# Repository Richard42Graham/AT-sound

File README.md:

# AT-sound 

AKA **ATST**: All terrain sound transport. 

A circuit board controlling a relay when audio cable is active.

## Use

Requires 5V power to operate. Provides 5V and common ground on relay pins when audio is detected.

## Contribution

Please contribute. 

## License

[CERN Open Hardware Licence](https://ohwr.org/cernohl)

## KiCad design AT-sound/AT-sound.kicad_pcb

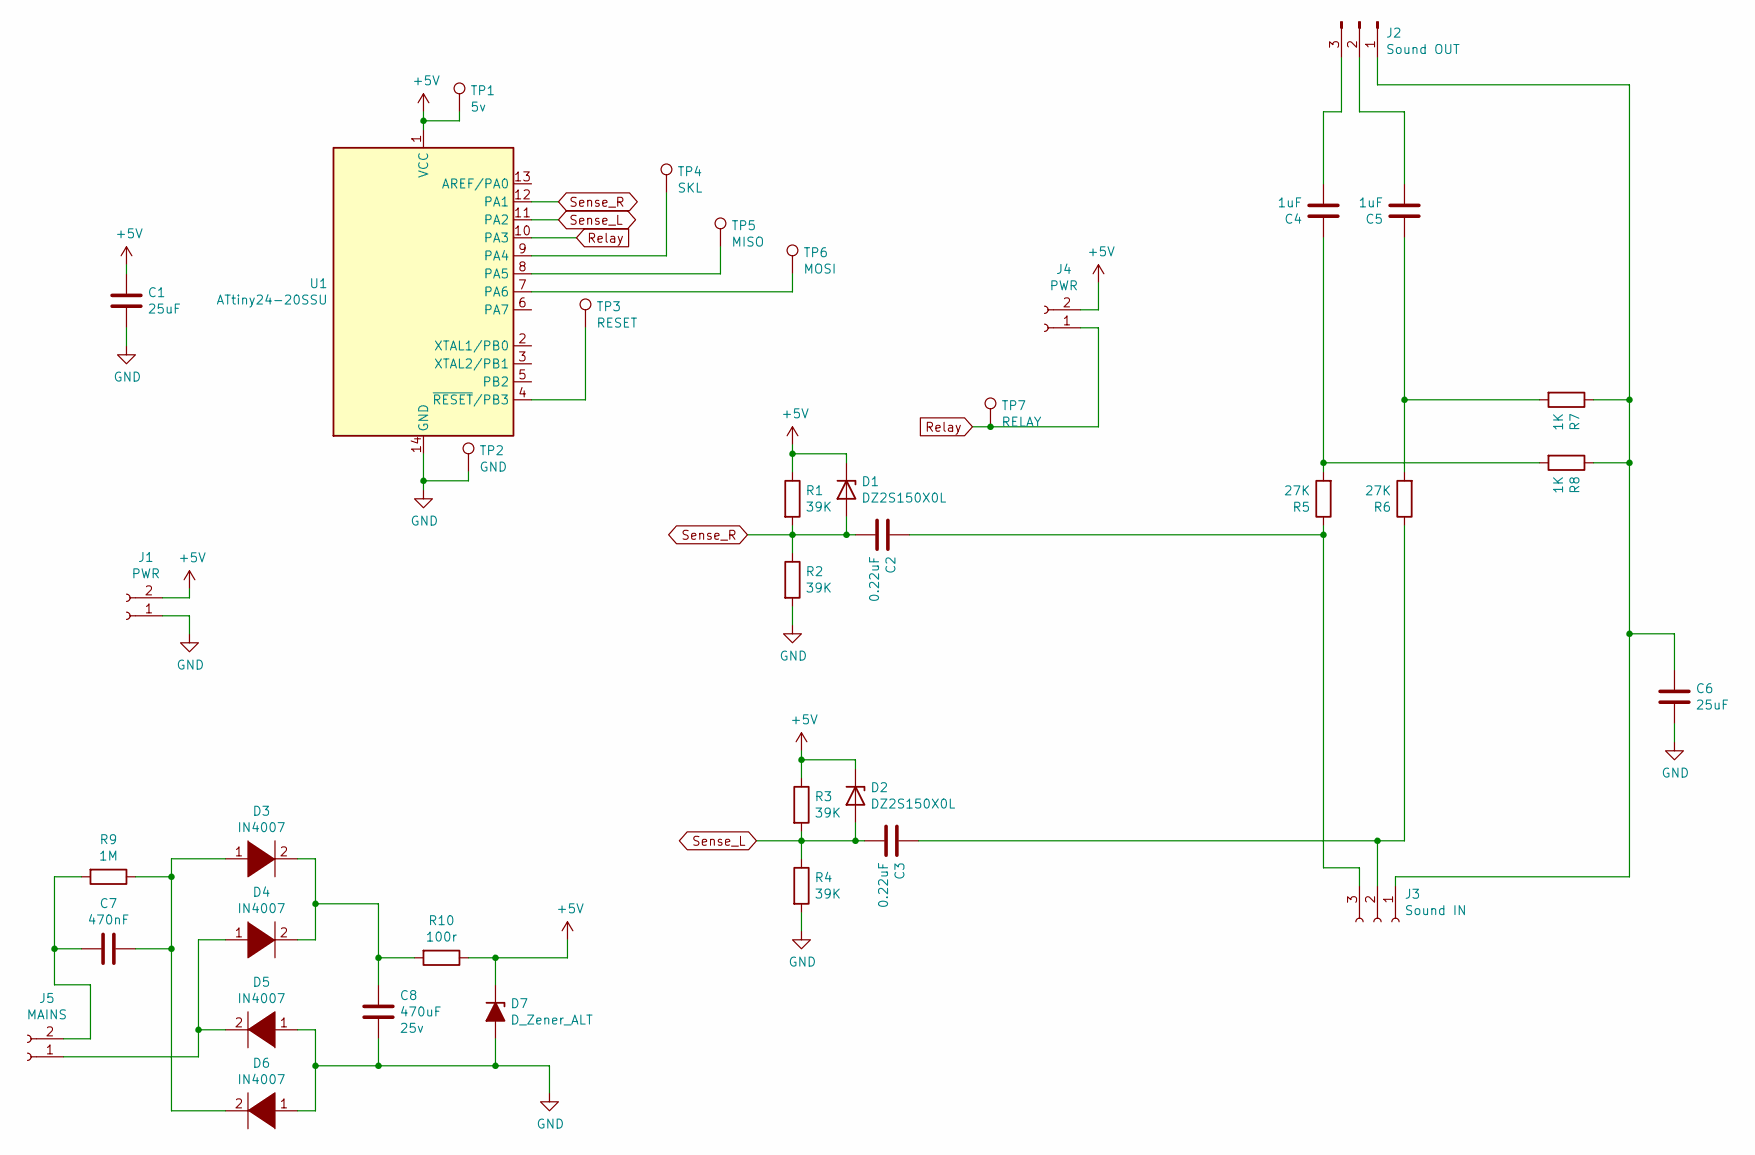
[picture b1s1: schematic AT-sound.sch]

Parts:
C1, C6: 25uF; C_0805_2012Metric
C2, C3: 0.22uF; C_0805_2012Metric
C4, C5: 1uF; C_0805_2012Metric
C7: 470nF; C_Radial_D12.5mm_H25.0mm_P5.00mm
C8: 470uF; C_Radial_D6.3mm_H5.0mm_P2.50mm; Voltage rating 25v
D1, D2: DZ2S150X0L; D_SOD-523
D3, D4, D5, D6: IN4007; D_A-405_P10.16mm_Horizontal
D7: D_Zener_ALT; D_T-1_P5.08mm_Horizontal
J1, J4: PWR; PinSocket_1x02_P2.54mm_Vertical
J2: Sound OUT; PinSocket_1x03_P2.54mm_Vertical
J3: Sound IN; PinSocket_1x03_P2.54mm_Vertical
J5: MAINS; PinSocket_1x02_P2.54mm_Vertical
R1, R2, R3, R4: 39K; R_0603_1608Metric
R5, R6: 27K; R_0603_1608Metric
R7, R8: 1K; R_0603_1608Metric
R9: 1M; R_Axial_DIN0207_L6.3mm_D2.5mm_P7.62mm_Horizontal
R10: 100r; R_Axial_DIN0207_L6.3mm_D2.5mm_P7.62mm_Horizontal
TP1: 5v; TestPoint_Pad_D1.0mm
TP2: GND; TestPoint_Pad_D1.0mm
TP3: RESET; TestPoint_Pad_D1.0mm
TP4: SKL; TestPoint_Pad_D1.0mm
TP5: MISO; TestPoint_Pad_D1.0mm
TP6: MOSI; TestPoint_Pad_D1.0mm
TP7: RELAY; TestPoint_Pad_D1.0mm
U1: ATtiny24-20SSU; SOIC-14_3.9x8.7mm_P1.27mm

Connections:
+5V: C1.1, D1.1 (K), D2.1 (K), D7.1 (K), J1.2, J4.2, R1.1, R3.1, R10.1, TP1.1, U1.1 (VCC)
GND: C1.2, C6.2, C8.1, D5.1 (K), D6.1 (K), D7.2 (A), J1.1, R2.2, R4.2, TP2.1, U1.14 (GND)
unnamed: C2.1, J3.3, R5.1
unnamed: C3.1, J3.2, R6.1
unnamed: C4.1, R5.2, R8.2
unnamed: C4.2, J2.3
unnamed: C5.1, R6.2, R7.2
unnamed: C5.2, J2.2
unnamed: C6.1, J2.1, J3.1, R7.1, R8.1
unnamed: C7.1, D3.1 (K), D6.2 (A), R9.1
unnamed: C7.2, J5.2, R9.2
unnamed: C8.2, D3.2 (A), D4.2 (A), R10.2
unnamed: D4.1 (K), D5.2 (A), J5.1
unnamed: TP3.1, U1.4 (~RESET~/PB3)
unnamed: TP4.1, U1.9 (PA4)
unnamed: TP5.1, U1.8 (PA5)
unnamed: TP6.1, U1.7 (PA6)
Relay: J4.1, TP7.1, U1.10 (PA3)
Sense_L: C3.2, D2.2 (A), R3.2, R4.1, U1.11 (PA2)
Sense_R: C2.2, D1.2 (A), R1.2, R2.1, U1.12 (PA1)

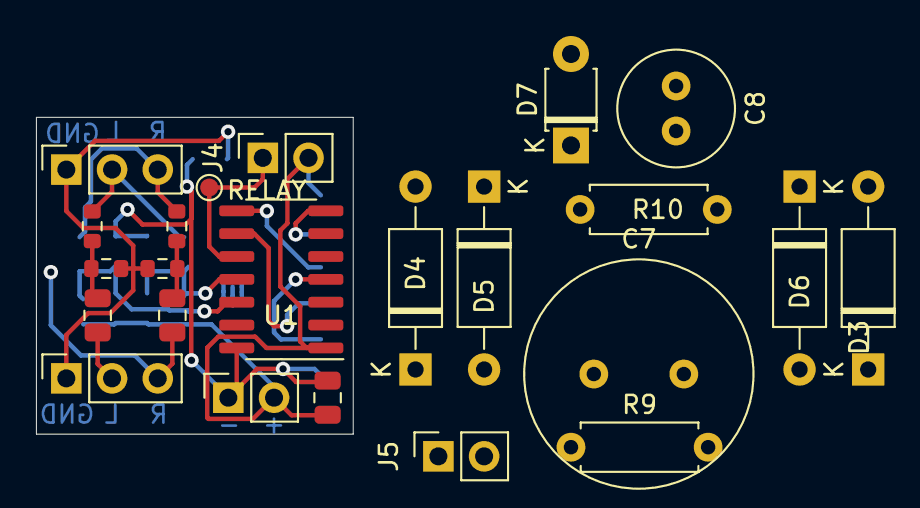
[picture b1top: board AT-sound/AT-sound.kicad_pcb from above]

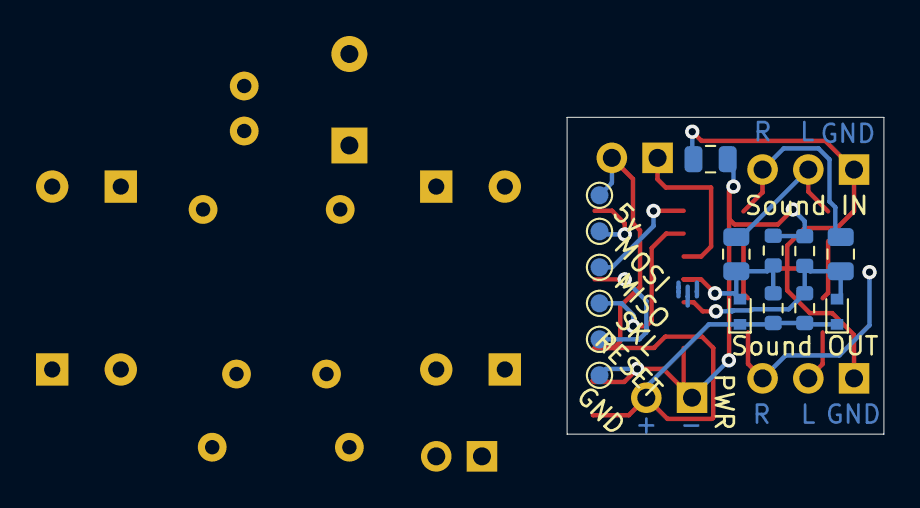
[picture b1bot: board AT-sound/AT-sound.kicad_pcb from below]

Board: 2 copper layers, 17.6 x 17.6 mm, 38 parts (15 on the bottom side), 20 nets.

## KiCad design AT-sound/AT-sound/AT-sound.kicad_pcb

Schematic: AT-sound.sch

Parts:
C1: 25uF; C_0805_2012Metric
C2, C3: 0.22uF; C_0805_2012Metric
D1, D2: DZ2S150X0L; D_SOD-523
J1: PWR; PinSocket_1x02_P2.54mm_Vertical
J2: Sound OUT; PinSocket_1x03_P2.54mm_Vertical
J3: Sound IN; PinSocket_1x03_P2.54mm_Vertical
Q1: AQY212S; SOT-23
R1, R2, R3, R4: 39K; R_0603_1608Metric
R5, R6: 700r; R_0603_1608Metric
TP1: 5v; TestPoint_Pad_D1.0mm
TP2: GND; TestPoint_Pad_D1.0mm
TP3: RESET; TestPoint_Pad_D1.0mm
TP4: SKL; TestPoint_Pad_D1.0mm
TP5: MISO; TestPoint_Pad_D1.0mm
TP6: MOSI; TestPoint_Pad_D1.0mm
TP7: RELAY; TestPoint_Pad_D1.0mm
U1: ATtiny24-20SSU; SOIC-14_3.9x8.7mm_P1.27mm
U2, U3: SFH617A-2X006; SOP-4_3.8x4.1mm_P2.54mm

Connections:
+5V: C1.1, D1.1 (K), D2.1 (K), J1.2, R1.1, R3.1, TP1.1, U1.1 (VCC), U2.1, U3.1
GND: C1.2, J1.1, J2.1, J3.1, Q1.2, R2.2, R4.2, TP2.1, U1.14 (GND)
unnamed: C2.1, J3.3, U2.3
unnamed: C3.1, J3.2, U3.3
unnamed: J2.2, U3.4
unnamed: J2.3, U2.4
unnamed: Q1.3, R5.2, R6.2
unnamed: R5.1, U2.2
unnamed: R6.1, U3.2
unnamed: TP3.1, U1.4 (~RESET~/PB3)
unnamed: TP4.1, U1.9 (PA4)
unnamed: TP5.1, U1.8 (PA5)
unnamed: TP6.1, U1.7 (PA6)
Relay: Q1.1, TP7.1, U1.10 (PA3)
Sense_L: C3.2, D2.2 (A), R3.2, R4.1, U1.11 (PA2)
Sense_R: C2.2, D1.2 (A), R1.2, R2.1, U1.12 (PA1)

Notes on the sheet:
opto cupler part number wrong.

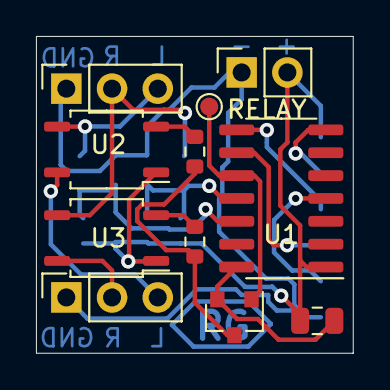
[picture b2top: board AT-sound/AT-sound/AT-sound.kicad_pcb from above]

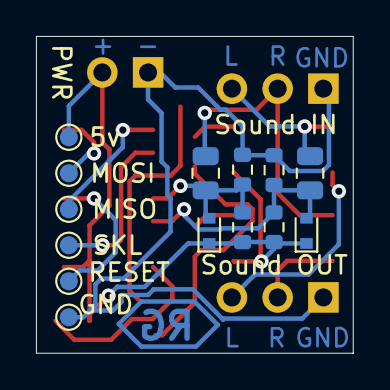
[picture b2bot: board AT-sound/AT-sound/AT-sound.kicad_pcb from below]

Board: 2 copper layers, 17.6 x 17.6 mm, 25 parts (14 on the bottom side), 16 nets.

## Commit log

2021-05-06 first commit of this project
2021-05-06 starred
2021-05-07 replaced the relays with optocuplers
2021-05-07 started layout and routing!
2021-05-07 did a little routing
2021-05-08 finished routing
2021-05-10 finished routing, questioning its existance
2021-05-10 made a external realay verant.
2021-05-10 added my smol logo
2021-05-11 added capacitive dropper cirict for POWERgit add *git add *git add *
2021-05-11 did a little layout for capacitve dropper
2021-05-11 Added README
2021-05-11 Added link to open hardware license
